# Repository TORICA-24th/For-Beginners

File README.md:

# For-Beginners
- [新入生教育実践編](https://www.notion.so/7874e2cedf9c4ff7b75fd1fb712b05d0)の解答
- プラクティスボードの回路図，PCBデータ，ガーバーファイル等

## PCB_PracticeBoard
### 使用している部品
- [DCジャック(18742)](https://akizukidenshi.com/catalog/g/gC-09408/)
- [LED](https://akizukidenshi.com/catalog/g/gI-06245/)
- [コンデンサ(4.7μ)](https://akizukidenshi.com/catalog/g/gP-17895/)
- [抵抗(10k)](https://akizukidenshi.com/catalog/g/gR-25103/)
- [Raspberry Pi Pico](https://akizukidenshi.com/catalog/g/gM-16132/)
- [タクトスイッチ(SW1,2,4,5)](https://akizukidenshi.com/catalog/g/gP-03647/)
- [トグルスイッチ(SW3)](https://akizukidenshi.com/catalog/g/gP-12406/)
- [可変抵抗(10k)](https://akizukidenshi.com/catalog/g/gP-08012/)
- [XHコネクタ(2ピン)](https://akizukidenshi.com/catalog/g/gC-12262/)
- [XHコネクタ(3ピン)](https://akizukidenshi.com/catalog/g/gC-12263/)

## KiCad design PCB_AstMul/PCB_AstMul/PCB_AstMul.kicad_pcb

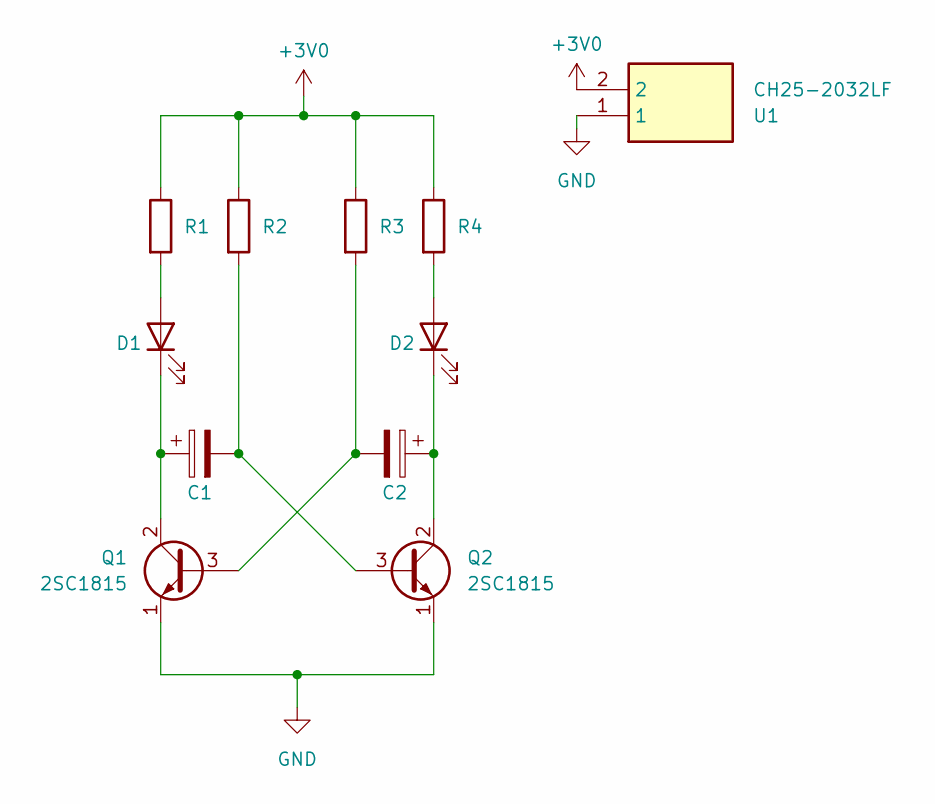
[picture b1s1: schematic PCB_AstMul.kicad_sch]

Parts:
C1, C2: C_Polarized; CP_Radial_D6.3mm_P2.50mm
D1, D2: LED; LED_D5.0mm
Q1, Q2: 2SC1815; TO-92_Inline
R1, R2, R3, R4: R; R_Axial_DIN0207_L6.3mm_D2.5mm_P10.16mm_Horizontal
U1: CH25-2032LF; CH252032LF; Manufacturer_Part_Number CH25-2032LF

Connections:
+3V0: R1.1, R2.1, R3.1, R4.1, U1.2
GND: Q1.1 (E), Q2.1 (E), U1.1
unnamed: D1.2 (A), R1.2
unnamed: C1.1, D1.1 (K), Q1.2 (C)
unnamed: D2.2 (A), R4.2
unnamed: C2.1, D2.1 (K), Q2.2 (C)
unnamed: C2.2, Q1.3 (B), R3.2
unnamed: C1.2, Q2.3 (B), R2.2

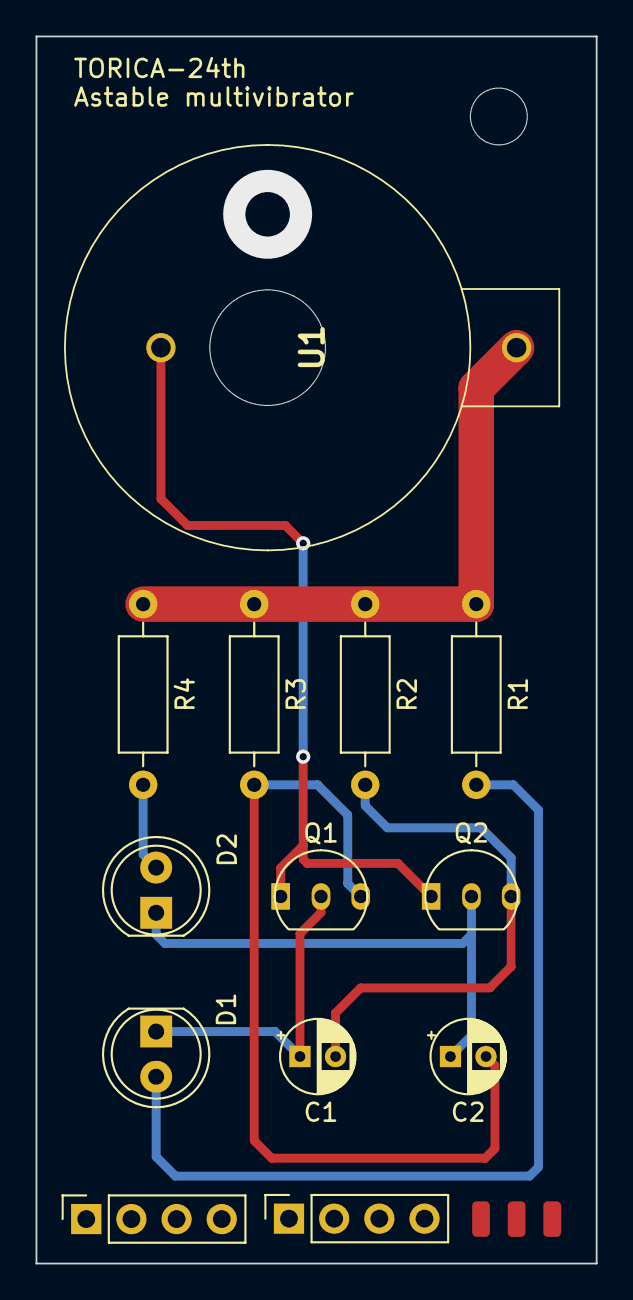
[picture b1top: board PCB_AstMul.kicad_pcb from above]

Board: 2 copper layers, 31.5 x 69.0 mm, 11 parts (0 on the bottom side), 8 nets.

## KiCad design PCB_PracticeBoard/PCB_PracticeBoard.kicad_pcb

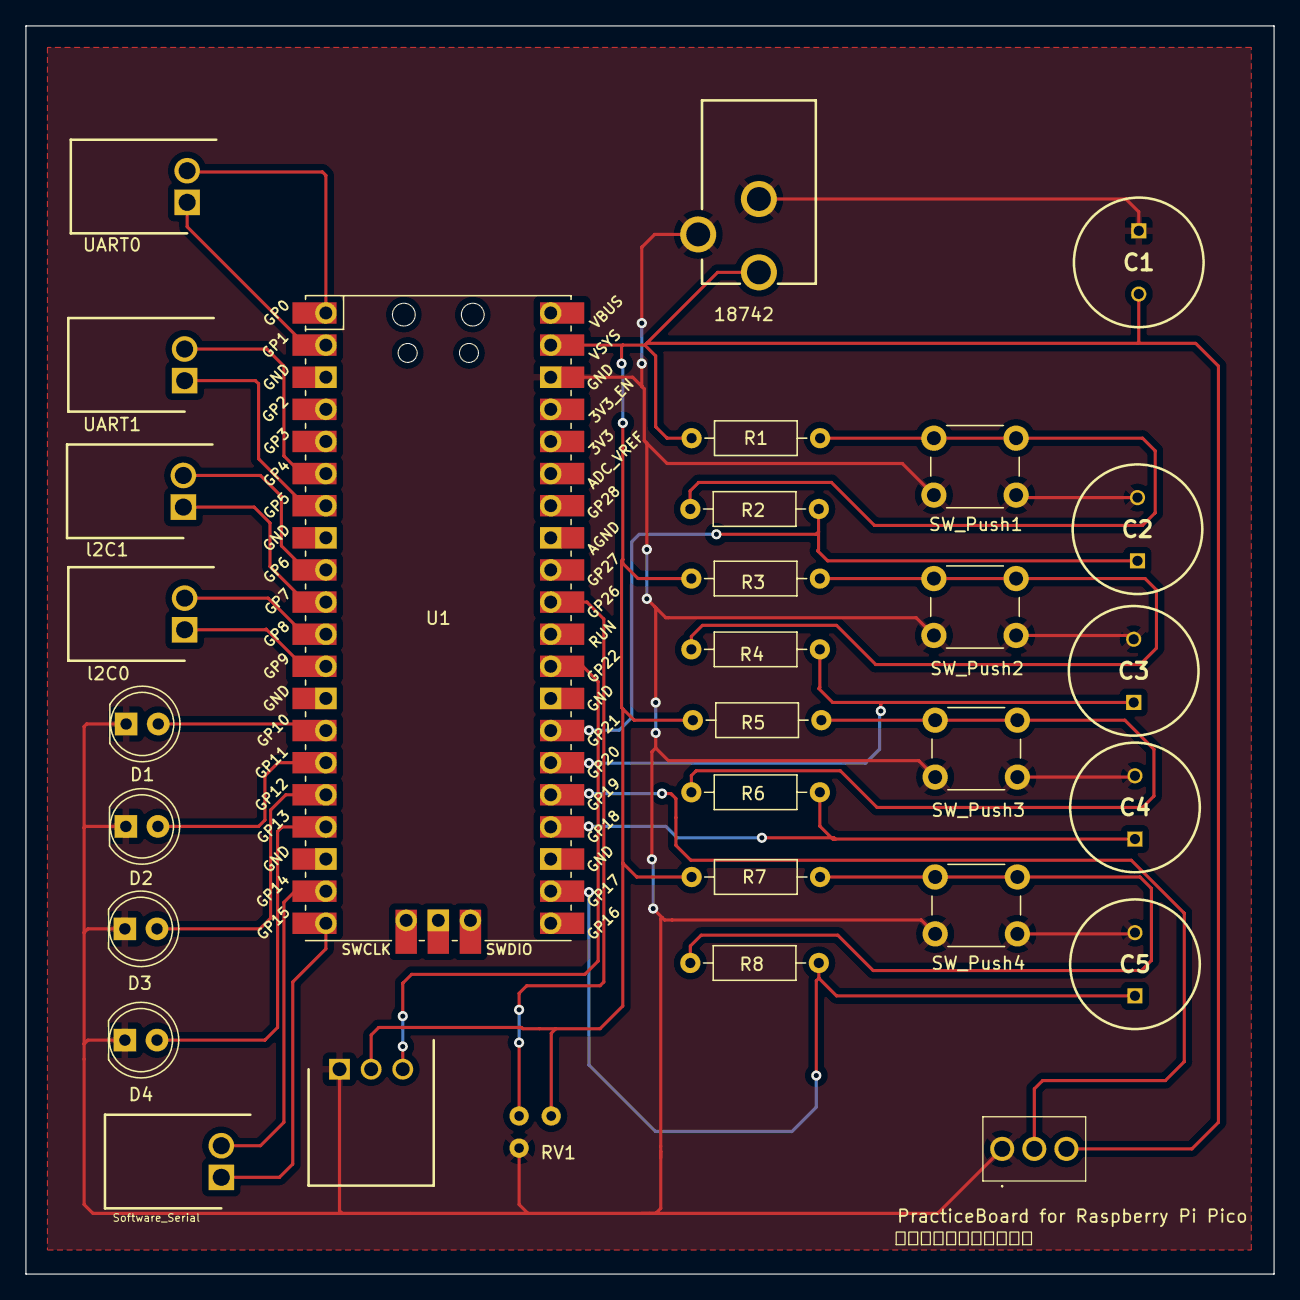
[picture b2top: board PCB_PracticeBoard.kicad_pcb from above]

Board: 2 copper layers, 98.7 x 98.7 mm, 31 parts (0 on the bottom side), 27 nets.

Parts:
C1, C2, C3, C4, C5: 4.7μ; CAPPRD500W60D1025H1400
D1, D2, D3, D4: LED; LED_D5.0mm
J1: UART0; SHDRRA2W80P0X250_1X2_740X1150X610P
J2: UART1; SHDRRA2W80P0X250_1X2_740X1150X610P
J3: I2C0; SHDRRA2W80P0X250_1X2_740X1150X610P
J4: I2C1; SHDRRA2W80P0X250_1X2_740X1150X610P
J5: Software_Serial; SHDRRA2W80P0X250_1X2_740X1150X610P
J6: Conn_01x03_Female; SHDRRA3W64P0X250_1X3_990X1150X610P
J7: 18742
R1, R2, R3, R4, R5, R6, R7, R8: 10k; R_Axial_DIN0207_L6.3mm_D2.5mm_P10.16mm_Horizontal
RV1: 10k; 3386K
SW1, SW2, SW4, SW5: SW_Push; SW_PUSH_6mm_H4.3mm
SW3: SW_DPDT_x2; 2MS1T2B4M2QES
U1: Pico; RPi_Pico_SMD_TH

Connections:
+5V: C1.2, J6.2, J7.1, R1.1, R3.1, R5.1, R7.1, RV1.1, SW3.3 (C), U1.39 (VSYS)
/LED1: D1.2 (A), U1.14 (GPIO10)
/LED2: D2.2 (A), U1.15 (GPIO11)
/LED3: D3.2 (A), U1.16 (GPIO12)
/LED4: D4.2 (A), U1.17 (GPIO13)
/SPK: J6.3, U1.29 (GPIO22)
/SW1: C2.1, R2.2, U1.27 (GPIO21)
/SW2: C3.1, R4.2, U1.26 (GPIO20)
/SW3: SW3.2 (B), U1.25 (GPIO19)
/SW4: C4.1, R6.2, U1.24 (GPIO18)
/SW5: C5.1, R8.2, U1.22 (GPIO17)
/VOL: RV1.2, U1.31 (GPIO26_ADC0)
GND: C1.1, C2.2, C3.2, C4.2, C5.2, D1.1 (K), D2.1 (K), D3.1 (K), D4.1 (K), J6.1, J7.2, J7.3, RV1.3, SW1.2, SW2.2, SW3.1 (A), SW4.2, SW5.2, U1.38 (GND)
unnamed: J1.1, U1.2 (GPIO1)
unnamed: J1.2, U1.1 (GPIO0)
unnamed: J2.1, U1.7 (GPIO5)
unnamed: J2.2, U1.6 (GPIO4)
unnamed: J3.1, U1.12 (GPIO9)
unnamed: J3.2, U1.11 (GPIO8)
unnamed: J4.1, U1.10 (GPIO7)
unnamed: J4.2, U1.9 (GPIO6)
unnamed: J5.1, U1.20 (GPIO15)
unnamed: J5.2, U1.19 (GPIO14)
unnamed: R1.2, R2.1, SW1.1
unnamed: R3.2, R4.1, SW2.1
unnamed: R5.2, R6.1, SW4.1
unnamed: R7.2, R8.1, SW5.1

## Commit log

2023-10-10 add PCB_PracticeBorad
2023-10-10 add PCB_PracticeBoard,update Readme
2023-10-26 Create CODEOWNERS
2023-11-01 create gerber files
2024-07-03 Organize 20240703
